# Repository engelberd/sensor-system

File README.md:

# sensor-system

This repository contains the full Sensor System project:

- `hardware/` for KiCad PCB projects, parts, footprints, and hardware notes
- `node/` for the Pico firmware and bootloader artifacts
- `host/` for the complete host product: configuration, operator support and runtime
- `host/runtime/` for the Rust recorder, protocol-6 contracts and data tools

Architecture and current implementation gates start at
[docs/README.md](docs/README.md). The supported local operator interface is
[hostctl v2](docs/architecture/HOSTCTL-V2.md).

For a macOS KiCad, firmware and host-development workstation, follow
[the macOS setup guide](docs/SETUP-MACOS.md), install declared tools with
`brew bundle --file Brewfile`, and run `./tools/check_macos.sh`.

The generated, ignored `host/system_config.json` extends a tracked profile from
`host/configs/systems/`. Product-wide defaults live in
`host/configs/common.json`; stable channel and sensor facts live in the system
profile; device paths, storage overrides and temporary disabled channels remain
in the local overlay. See [the repository structure](docs/REPOSITORY-STRUCTURE.md)
and validate an installation with:

```bash
./hostctl doctor --config host/system_config.json
```

Release validation and publication are described in
[RELEASING.md](RELEASING.md), and notable changes are listed in
[CHANGELOG.md](CHANGELOG.md).

Local runtime output has one predictable layout:

- `var/recordings/` for new measurements
- `var/archive/` for compacted archives
- `var/log/` for host logs and events
- `var/tmp/` for temporary artifacts
- `/run/sensor-system/` for locks, commands and live status

These directories are not versioned. Use `./hostctl paths` to display the
effective paths for the active host configuration.

Every installed node has an immutable hardware revision. Revision `2` is the
currently installed wiring (SCK 14, MOSI 15, DRDY 11, INT1 10, no DE GPIO),
while revision `1` uses SCK 10, MOSI 11, DRDY 14, INT1 15 and DE on GPIO2.
Node IDs and sensor settings remain runtime configuration independent of that
revision.

## Repository Notes

In this Codex workspace the top-level `.git/` path is reserved by the
environment, so repository metadata lives in `.git-main/` and the local wrapper
`./sgit` should be used instead of plain `git`.

Suggested day-to-day workflow in this workspace:

1. Make changes locally in this repository.
2. Use `./sgit ...` for repository commands in this environment.
3. Commit before flashing or deploying to another device.
4. Push to your remote.
5. On the Raspberry Pi host, run `git pull`, build from `node/`, and flash the selected artifact.

## Local Bring-Up On A New Computer

If you are building and flashing from a local Linux or macOS machine instead of
the Raspberry Pi host:

1. Clone the repository and enter it.
2. Install the Pico SDK and toolchain.
3. Build `node/`.
4. Flash `node/build/sensor-system-node-factory.uf2` onto a brand-new Pico 2.
5. Build the host with `./hostctl build`.
6. Identify the node read-only with `./hostctl node identify DEVICE ADDRESS 115200`.

Example setup for a clean local checkout:

```bash
git clone git@github.com:engelberd/sensor-system.git
cd sensor-system
git clone https://github.com/raspberrypi/pico-sdk.git
export PICO_SDK_PATH=$PWD/pico-sdk
python3 -m venv host/.venv
host/.venv/bin/python -m pip install -r host/requirements-recorder.txt
```

The local `pico-sdk/` checkout is intentionally ignored and is not a submodule.
Each build host may keep the SDK elsewhere and point `PICO_SDK_PATH` to it.

On macOS with Homebrew, the typical firmware toolchain is:

```bash
brew install cmake picotool arm-none-eabi-gcc
```

Build the node firmware with explicit compiler paths when needed:

```bash
cmake -S node --preset board-v2 \
  -DCMAKE_C_COMPILER=/opt/homebrew/bin/arm-none-eabi-gcc \
  -DCMAKE_CXX_COMPILER=/opt/homebrew/bin/arm-none-eabi-g++ \
  -DCMAKE_ASM_COMPILER=/opt/homebrew/bin/arm-none-eabi-gcc
cmake --build node/build
```

For a V1 board use `cmake -S node --preset board-v1` followed by
`cmake --build node/build.v1`. Never reuse one build directory for both board
revisions.

The most important output files are:

- `node/build/sensor-system-node-factory.uf2` for first-time USB/BOOTSEL flashing
- `node/build/sensor-system-node.uf2` as the general full-image UF2
- `node/build/sensor-system-node-update-package.json` for later RS485 updates

Further details live in:

- [hardware/README.md](hardware/README.md)
- [node/README-bootloader.md](node/README-bootloader.md)
- [host/README-product.md](host/README-product.md)
- [host/README-deploy.md](host/README-deploy.md)

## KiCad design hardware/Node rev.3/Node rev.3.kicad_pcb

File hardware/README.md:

# Hardware

Hardware design files for the Sensor System project.

Current KiCad project:

- `KiCad - node V2/RP2350.kicad_pro`

The directory name is historical. This is an unreleased custom-board design,
not the definition of the V2 boards installed in Sanok. Installed V2 wiring is
defined by `node/config/board_profile.h`: SCK 14, MOSI 15, MISO 12, CS 13,
DRDY 11, INT1 10 and no firmware-controlled DE pin. Do not change the firmware
revision map from the in-progress KiCad project without a physical bring-up and
an explicit new board revision.

## Repository layout

This project should stay as one GitHub repository for now:

- `hardware/` - KiCad projects, PCB notes, parts, footprints, manufacturing files
- `node/` - RP2350/Pico firmware
- `host/` - host tools, recorder, dashboards, deployment files

This is a monorepo layout. It is simpler than a nested Git repository and makes
hardware/software changes easy to review together. A separate hardware repository
or Git submodule only starts to pay off if the PCB must be shared with a different
team, licensed differently, or released on a different schedule.

## What is tracked

Track these files:

- `*.kicad_pro`
- `*.kicad_sch`
- `*.kicad_pcb`
- project-local `*.kicad_sym` files
- project-local `*.pretty/*.kicad_mod` footprint libraries
- selected 3D models used by footprints
- documentation in this directory
- released fabrication outputs in a named release folder, if needed

Do not track these files:

- `*.kicad_prl`
- `*-backups/`
- `fp-info-cache`
- local lock/temp files
- `.DS_Store`

## Collaboration rules

- Commit before making large schematic rewires or PCB placement changes.
- Pull before opening KiCad if someone else may have pushed hardware changes.
- Avoid editing the same schematic sheet or PCB placement in parallel.
- For footprint changes, edit project-local libraries first, then update the
  board from the library and commit both the library change and board change.
- Put part decisions in `parts.md` before layout, especially when package,
  stock, or footprint choice matters.
- Put JLCPCB/LCSC assembly candidates and stock checks in `jlcpcb-parts.md`.
- Put layout/manufacturing decisions in `design-notes.md`.
- Track current work, assumptions, tasks, and completed items in `progress.md`.

## Opening the project

Open this file in KiCad:

```text
hardware/KiCad - node V2/RP2350.kicad_pro
```

If a footprint is missing, first check the project-local library:

```text
hardware/KiCad - node V2/my_footprints.pretty
```

Vendor downloads and raw imported libraries can stay locally in
`footprints.extra/`, which is ignored by Git. After checking a vendor footprint,
copy the cleaned version into `my_footprints.pretty` so everyone gets the same
reviewed footprint.

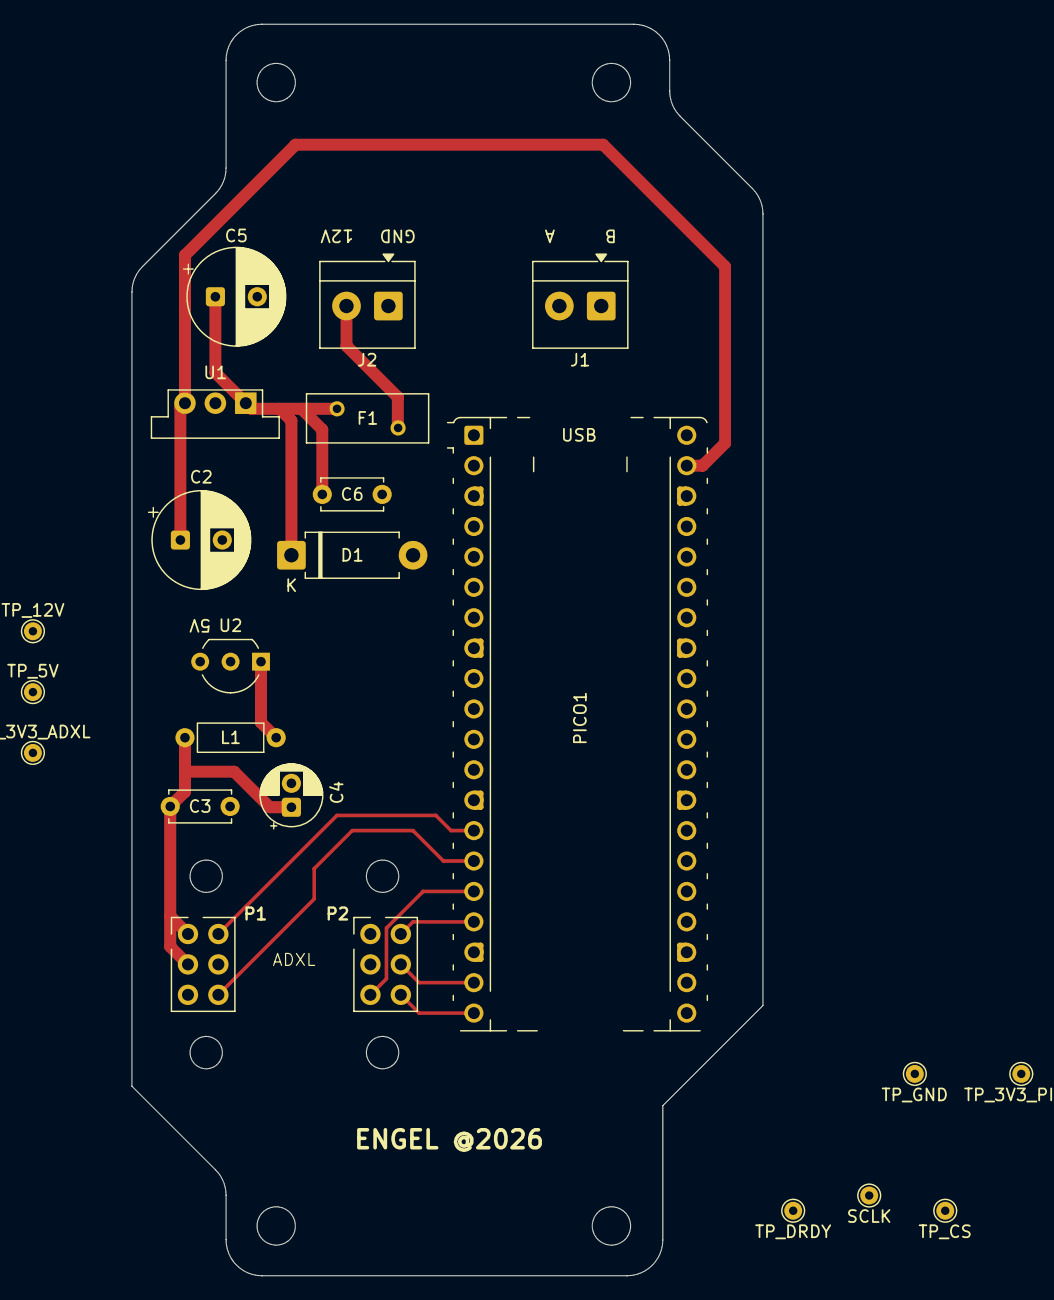
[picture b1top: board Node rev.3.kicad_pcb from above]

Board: 2 copper layers, 52.7 x 104.5 mm, 26 parts (0 on the bottom side), 13 nets.

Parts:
C2: 220uF; CP_Radial_D8.0mm_P3.50mm
C3, C6: 100nF; C_Disc_D5.0mm_W2.5mm_P5.00mm
C4: 10uF; CP_Radial_D5.0mm_P2.00mm
C5: 470uF; CP_Radial_D8.0mm_P3.50mm
D1: P6KE15A-DIO; D_DO-15_P10.16mm_Horizontal
F1: MF-R050; Fuse_BelFuse_0ZRE0016FF_L9.9mm_W3.8mm
H1, H2, H3, H4: MountingHole; MountingHole_3.2mm_M3
J1, J2: Screw_Terminal_01x02; TerminalBlock_4Ucon_1x02_P3.50mm_Horizontal
L1: FRH035080-A; L_Axial_L5.3mm_D2.2mm_P7.62mm_Horizontal_Vishay_IM-1
MOD1: EVAL-ADXL355Z
PICO1: RaspberryPi_Pico; RaspberryPi_Pico_Common_Unspecified
TP1: TP_5V; TestPoint_THTPad_D1.5mm_Drill0.7mm
TP2: TP_GND; TestPoint_THTPad_D1.5mm_Drill0.7mm
TP3: TP_12V; TestPoint_THTPad_D1.5mm_Drill0.7mm
TP6: TP_3V3_ADXL; TestPoint_THTPad_D1.5mm_Drill0.7mm
TP7: TP_3V3_PICO; TestPoint_THTPad_D1.5mm_Drill0.7mm
TP8: SCLK; TestPoint_THTPad_D1.5mm_Drill0.7mm
TP9: TP_CS; TestPoint_THTPad_D1.5mm_Drill0.7mm
TP10: TP_DRDY; TestPoint_THTPad_D1.5mm_Drill0.7mm
U1: OKI-78SR-5_1_5-W36-C; Converter_DCDC_Murata_OKI-78SR_Vertical
U2: LP2950CZ-3.3/NOPB; TO-92_Inline_Wide

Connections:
/3V3_ADXL: C3.1, C4.1, L1.2, MOD1.1 (VDDIO), MOD1.3 (VDD), TP6.1 (1_1)
/3V3_Pico: PICO1.36 (3V3), TP7.1 (1_1)
/5V: C2.1, PICO1.39 (VSYS), TP1.1 (1_1), U1.3 (Positive_Output), U2.3 (IN)
/12VIN: F1.2, J2.2
/ADXL CS: MOD1.8 (CS/SCL), PICO1.17 (GPIO13), TP9.1 (1_1)
/ADXL DRDY: MOD1.6 (DRDY), PICO1.15 (GPIO11), TP10.1 (1_1)
/ADXL INT1: MOD1.2 (INT1), PICO1.14 (GPIO10)
/ADXL SCLK: MOD1.10 (SCLK/VSSIO), PICO1.19 (GPIO14), TP8.1 (1_1)
/ADXL SDI: MOD1.12 (MOSI/SDA), PICO1.20 (GPIO15)
/ADXL SDO: MOD1.11 (MISO/SDA), PICO1.16 (GPIO12)
GND: C2.2, C3.2, C4.2, C5.2, C6.2, D1.2 (A), J2.1, MOD1.5 (GND), PICO1.3 (GND), PICO1.8 (GND), PICO1.13 (GND), PICO1.18 (GND), PICO1.23 (GND), PICO1.28 (GND), PICO1.38 (GND), TP2.1 (1_1), U1.2 (Common_(Ground)), U2.2 (GND)
unnamed: C5.1, C6.1, D1.1 (K), F1.1, TP3.1 (1_1), U1.1 (Positive_Input)
unnamed: L1.1, U2.1 (OUT)

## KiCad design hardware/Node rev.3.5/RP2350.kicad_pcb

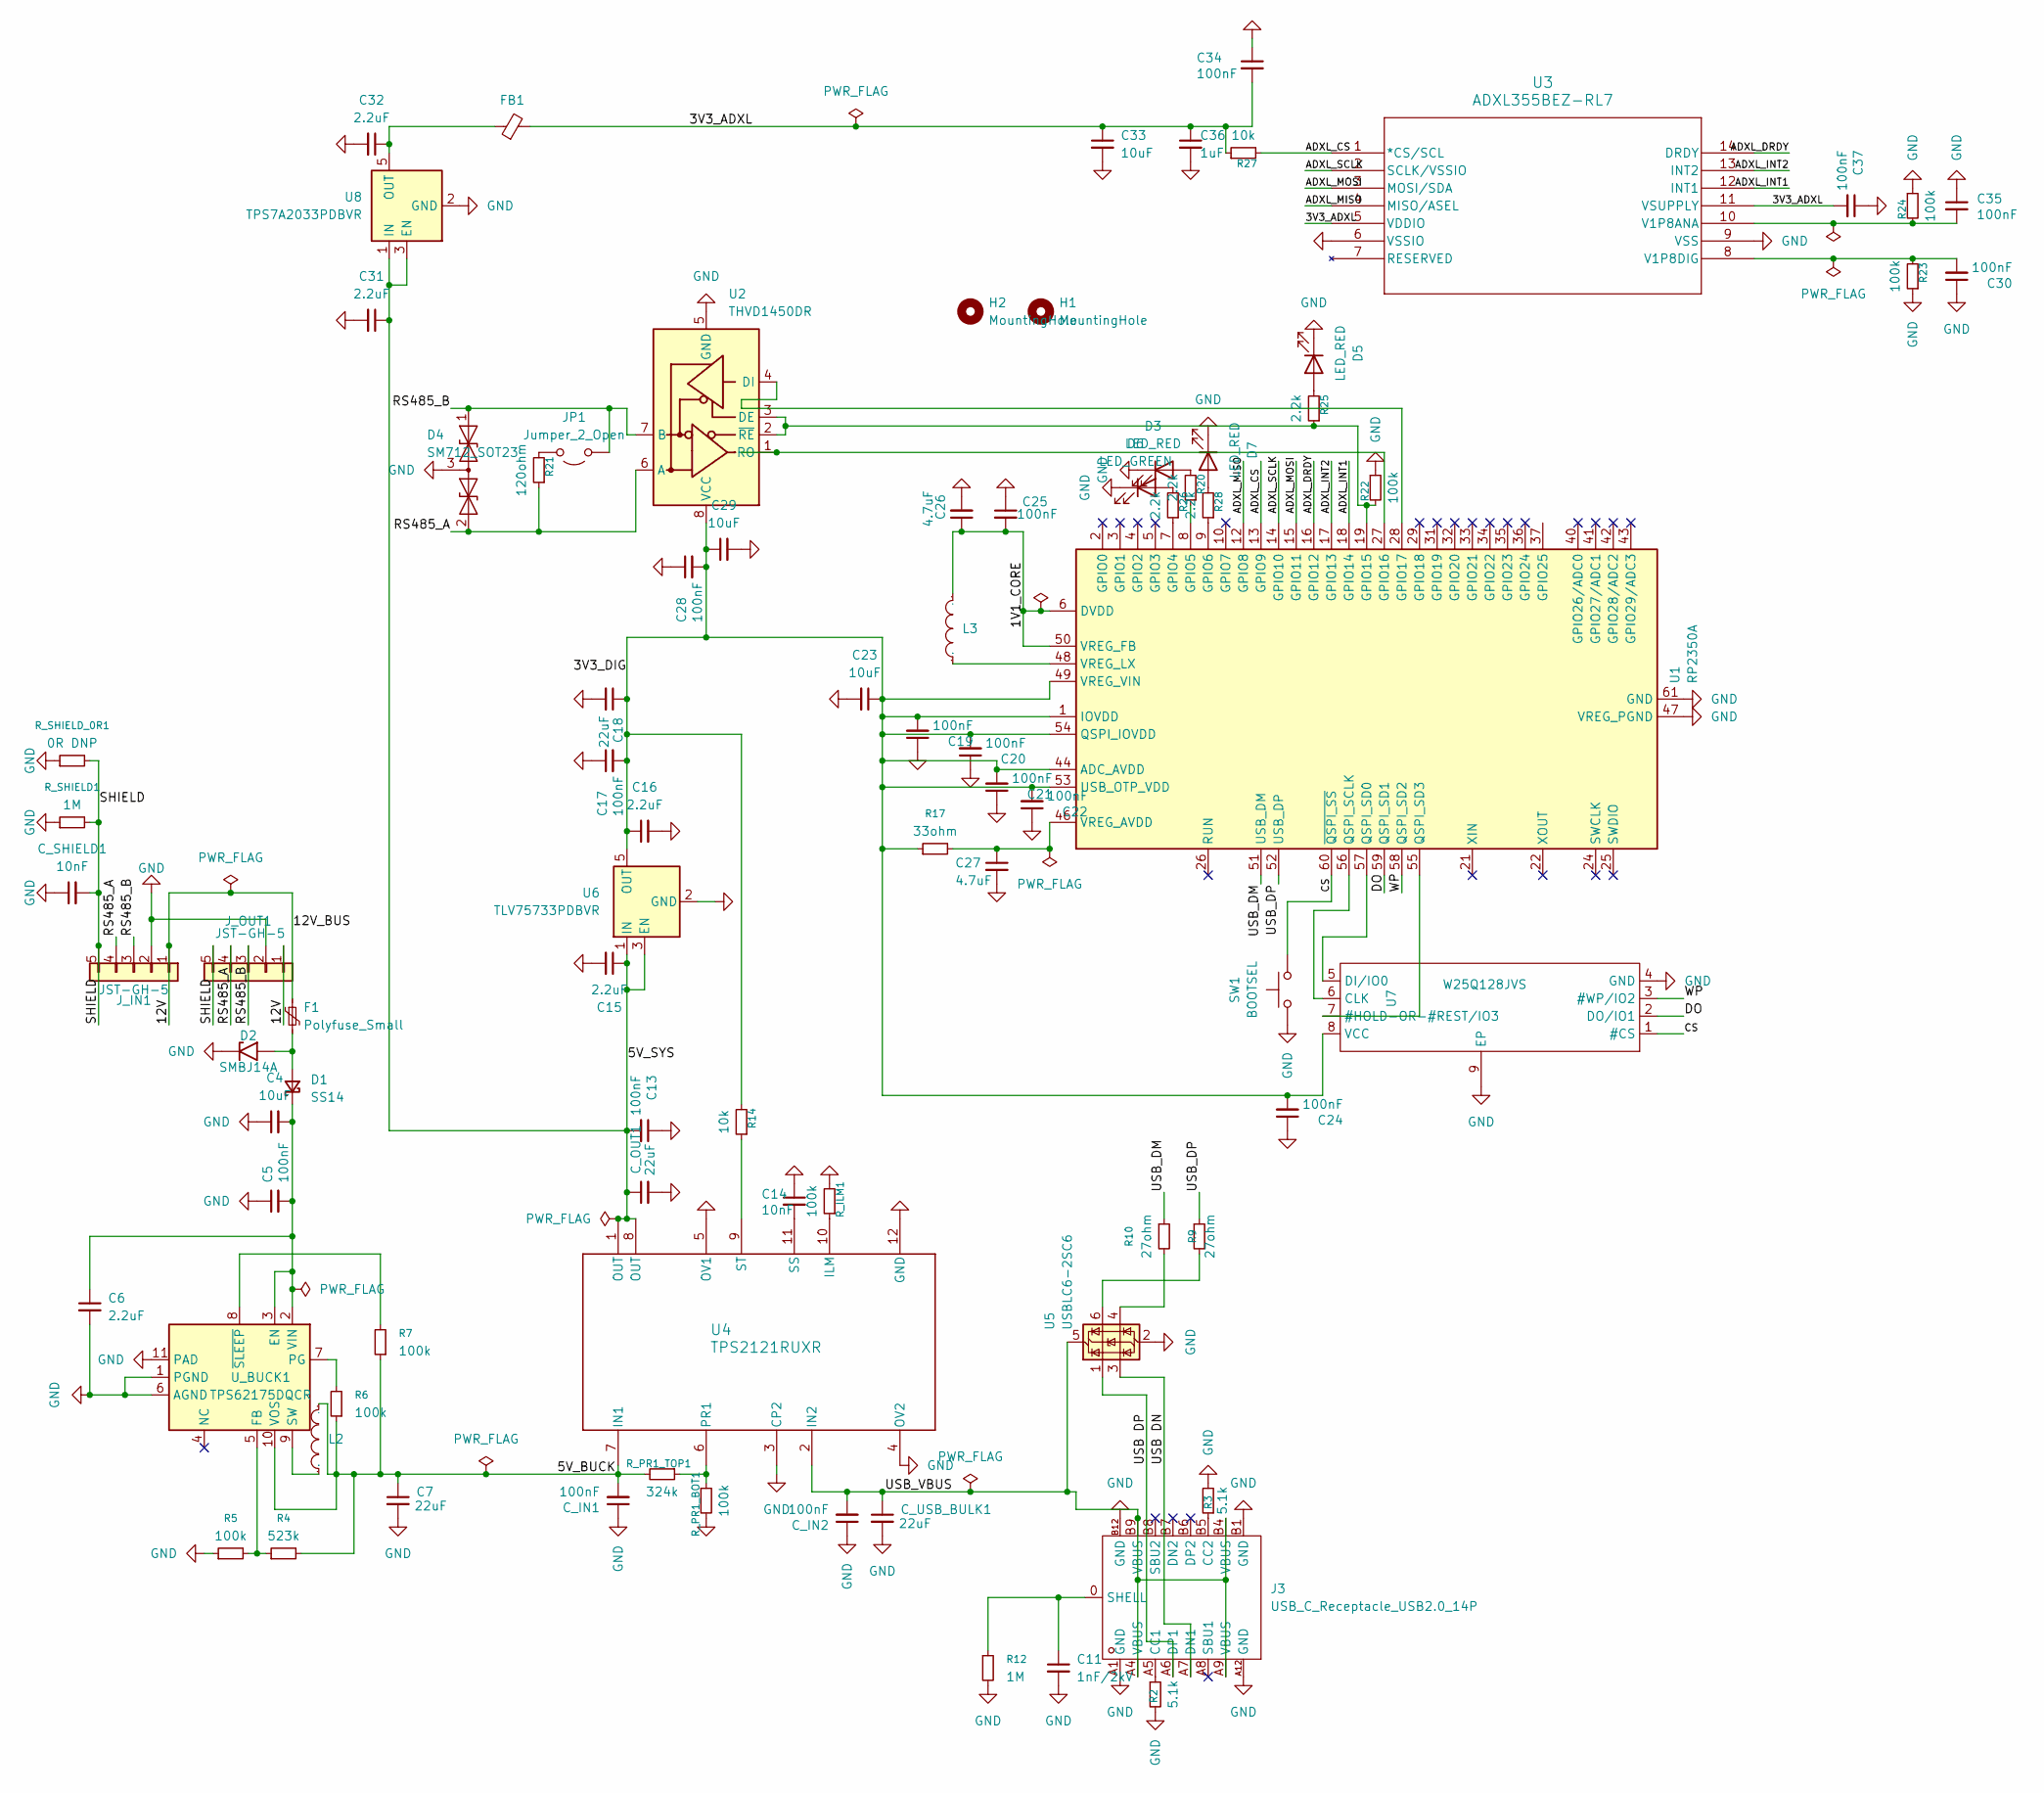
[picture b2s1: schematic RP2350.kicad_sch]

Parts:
C4, C29, C33: 10uF; C_0805_2012Metric
C5, C17, C28: 100nF; C_0603_1608Metric
C6, C15, C16, C31, C32: 2.2uF; C_0805_2012Metric
C7, C18: 22uF; C_0805_2012Metric
C11: 1nF/2kV; C_1206_3216Metric
C13, C19, C20, C21, C22, C24, C25, C30, C34, C35, C37: 100nF; C_0402_1005Metric
C14: 10nF; C_0603_1608Metric
C23: 10uF; C_0603_1608Metric
C26: 4.7uF; C_0603_1608Metric
C27: 4.7uF; C_0805_2012Metric
C36: 1uF; C_0603_1608Metric
C_IN1, C_IN2: 100nF; C_0402_1005Metric
C_OUT1: 22uF; C_0805_2012Metric
C_SHIELD1: 10nF; C_0805_2012Metric
C_USB_BULK1: 22uF; C_0805_2012Metric
D1: SS14; D_SMA; Manufacturer Part SS14; JLCPC# SS14
D2: SMBJ14A; D_SMB; Manufacturer Part SMBJ14A; JLCPC# C29937
D3, D5, D7: LED_RED; LED_0603_1608Metric; Manufacturer Part KT-0603R; JLCPC# 0603
D4: SM712_SOT23; SOT-23; Manufacturer Part SM712.TCT; JLCPC# C12067
D6: LED_GREEN; LED_0805_2012Metric; Manufacturer Part KT-0805G; JLCPC# C2297
F1: Polyfuse_Small; Fuse_1812_4532Metric; Manufacturer Part 1812L150/24MR; JLCPC# C142805
FB1: FerriteBead_S; L_0805_2012Metric; Manufacturer Part MPZ2012S601AT000; JLCPC# C21519
H1, H2: MountingHole; MountingHole_2.5mm
J3: USB_C_Receptacle_USB2.0_14P; USB-C-SMD_GT-USB-7051A; Manufacturer Part GT-USB-7051A; LCSC Part Name Type-C 母 立贴
JP1: Jumper_2_Open; SolderJumper-2_P1.3mm_Open_Pad1.0x1.5mm
J_IN1: JST-GH-5; CONN-SMD_BM05B-GHS-TBT; Manufacturer Part BM05B-GHS-TBT(LF)(SN)(N); JLCPC# C189891
J_OUT1: JST-GH-5; CONN-SMD_BM05B-GHS-TBT; Manufacturer Part BM05B-GHS-TBT(LF)(SN)(N); JLCPC# C189891
L2: 10uH; FXL0420-100-MIND-SMD_L4.4-W4.2; Manufacturer Part FXL0420-100-M; LCSC Part Name 10uH ±20% 2.2A
L3: 3.3uH; IND-SMD_L2.0-W1.6_AOTA-B201610S3R3-101-T; Manufacturer Part AOTA-B201610S3R3-101-T; LCSC Part Name 3.3uH 2.4A
R2, R3: 5.1k; R_0402_1005Metric
R4: 523k; R_0402_1005Metric
R5, R6, R7, R23, R24: 100k; R_0402_1005Metric
R9, R10: 27ohm; R_0402_1005Metric
R12: 1M; R_0603_1608Metric
R14, R27: 10k; R_0402_1005Metric
R17: 33ohm; R_0402_1005Metric
R20, R25, R26, R28: 2.2k; R_0402_1005Metric
R21: 120ohm; R_0805_2012Metric
R22: 100k; R_0603_1608Metric
R_ILM1: 100k; R_0402_1005Metric
R_PR1_BOT1: 100k; R_0402_1005Metric
R_PR1_TOP1: 324k; R_0402_1005Metric
R_SHIELD1: 1M; R_0603_1608Metric
R_SHIELD_0R1: 0R DNP; R_0805_2012Metric
SW1: BOOTSEL; KEY-SMD_4P-L4.2-W3.2-P2.20-LS4.6; Manufacturer Part SKRPACE010; JLCPC# C139797
U1: RP2350A; QFN-60-1EP_7x7mm_P0.4mm_EP3.4x3.4mm; JLCPC# C42411118
U2: THVD1450DR; THVD1450DR-SOIC-8_L4.9-W3.9-P1.27-LS6.0-BL; JLCPC# C2671361
U3: ADXL355BEZ-RL7; JLCPC# C515892
U4: TPS2121RUXR; TPS2121RUXR-VQFN-HR-12_L2.5-W2.0-P0.50-BL; JLCPC# C485916
U5: USBLC6-2SC6; JLCPC# C7519
U6: TLV75733PDBVR; TLV75733PDBVR-SOT-23-5_L2.9-W1.6-P0.95-LS2.8-BL; Manufacturer Part TLV75733PDBVR; JLCPC# C485517
U7: W25Q128JVS; WSON-8_L6.0-W5.0-P1.27-BL-EP; Manufacturer Part W25Q128JVPIQ; LCSC Part Name 支持双路/四路SPI接口的3V、128Mbit 串行闪存
U8: TPS7A2033PDBVR; Manufacturer Part TPS7A2033PDBVR; JLCPC# C2862740
U_BUCK1: TPS62175DQCR; TPS62175DQCR_WSON-10_L3.0-W2.0-P0.50-BL-EP; Manufacturer Part TPS62175DQCR; LCSC C32097

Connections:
/1V1_CORE: C25.2, C26.1, L3.2, U1.6 (DVDD), U1.23 (DVDD), U1.39 (DVDD), U1.50 (VREG_FB)
/3V3_ADXL: C33.1, C34.2, C36.1, C37.2, FB1.2, R27.1, U3.5 (VDDIO), U3.11 (VSUPPLY)
/3V3_DIG: C16.1, C17.2, C18.1, C19.2, C20.2, C21.2, C22.2, C23.1, C24.2, C28.2, C29.1, R14.2, R17.1, U1.1 (IOVDD), U1.11 (IOVDD), U1.20 (IOVDD), U1.30 (IOVDD), U1.38 (IOVDD), U1.44 (ADC_AVDD), U1.45 (IOVDD), U1.49 (VREG_VIN), U1.53 (USB_OTP_VDD), U1.54 (QSPI_IOVDD), U2.8 (VCC), U6.5 (OUT), U7.8 (VCC)
/5V_BUCK: C7.1, C_IN1.2, L2.2, R4.2, R6.1, R7.1, R_PR1_TOP1.2, U4.7 (IN1), U_BUCK1.10 (VOS)
/5V_SYS: C13.2, C15.1, C31.1, C_OUT1.1, U4.1 (OUT), U4.8 (OUT), U6.1 (IN), U6.3 (EN), U8.1 (IN), U8.3 (EN)
/12V: F1.1, J_IN1.1 (12V), J_OUT1.1 (12V)
/ADXL_CS: R27.2, U1.13 (GPIO9), U3.1 (*CS/SCL)
/ADXL_DRDY: U1.16 (GPIO12), U3.14 (DRDY)
/ADXL_INT1: U1.18 (GPIO14), U3.12 (INT1)
/ADXL_INT2: U1.17 (GPIO13), U3.13 (INT2)
/ADXL_MISO: U1.12 (GPIO8), U3.4 (MISO/ASEL)
/ADXL_MOSI: U1.15 (GPIO11), U3.3 (MOSI/SDA)
/ADXL_SCLK: U1.14 (GPIO10), U3.2 (SCLK/VSSIO)
/CS: SW1.2, U1.60 (~QSPI_SS), U7.1 (#CS)
/DO: U1.59 (QSPI_SD1), U7.2 (DO/IO1)
/RS485_A: D4.2 (A2), J_IN1.4 (A), J_OUT1.4 (A), R21.1, U2.6 (A)
/RS485_B: D4.1 (A1), JP1.1 (A), J_IN1.3 (B), J_OUT1.3 (B), U2.7 (B)
/SHIELD: C_SHIELD1.2, J_IN1.5 (SHIELD), J_OUT1.5 (SHIELD), R_SHIELD1.2, R_SHIELD_0R1.2
/USB DN: J3.A7 (DN1), U5.3 (I/O2)
/USB DP: J3.A6 (DP1), U5.1 (I/O1)
/USB_DM: R10.1, U1.51 (USB_DM)
/USB_DP: R9.1, U1.52 (USB_DP)
/USB_VBUS: C_IN2.2, C_USB_BULK1.1, J3.A4 (VBUS), J3.A9 (VBUS), J3.B4 (VBUS), J3.B9 (VBUS), U4.2 (IN2), U5.5 (VBUS)
/WP: U1.58 (QSPI_SD2), U7.3 (#WP/IO2)
GND: C4.1, C5.1, C6.2, C7.2, C11.2, C13.1, C14.1, C15.2, C16.2, C17.1, C18.2, C19.1, C20.1, C21.1, C22.1, C23.2, C24.1, C25.1, C26.2, C27.2, C28.1, C29.2, C30.1, C31.2, C32.2, C33.2, C34.1, C35.1, C36.2, C37.1, C_IN1.1, C_IN2.1, C_OUT1.2, C_SHIELD1.1, C_USB_BULK1.2, D2.1 (A1), D3.1 (K), D4.3 (common), D5.1 (K), D6.1 (K), D7.1 (K), J3.A1 (GND), J3.A12 (GND), J3.B1 (GND), J3.B12 (GND), J_IN1.2 (GND), J_OUT1.2 (GND), R2.2, R3.2, R5.1, R12.2, R22.1, R23.1, R24.1, R_ILM1.2, R_PR1_BOT1.2, R_SHIELD1.1, R_SHIELD_0R1.1, SW1.1, U1.47 (VREG_PGND), U1.61 (GND), U2.5 (GND), U3.6 (VSSIO), U3.9 (VSS), U4.3 (CP2), U4.4 (OV2), U4.5 (OV1), U4.12 (GND), U5.2 (GND), U6.2 (GND), U7.4 (GND), U7.9 (EP), U8.2 (GND), U_BUCK1.1 (PGND), U_BUCK1.6 (AGND), U_BUCK1.11 (PAD)
unnamed: D1.2 (A), D2.2 (A2), F1.2
unnamed: C4.2, C5.2, C6.1, D1.1 (K), U_BUCK1.2 (VIN), U_BUCK1.3 (EN)
unnamed: D3.2 (A), R20.2
unnamed: D5.2 (A), R25.2
unnamed: D6.2 (A), R26.2
unnamed: D7.2 (A), R28.2
unnamed: J3.A5 (CC1), R2.1
unnamed: J3.B5 (CC2), R3.1
unnamed: C11.1, J3.0 (SHELL), R12.1
unnamed: JP1.2 (B), R21.2
unnamed: R9.2, U5.6 (I/O1)
unnamed: R10.2, U5.4 (I/O2)
unnamed: R26.1, U1.7 (GPIO4)
unnamed: R20.1, U1.8 (GPIO5)
unnamed: R28.1, U1.9 (GPIO6)
unnamed: R22.2, R25.1, U1.19 (GPIO15), U2.2 (~RE), U2.3 (DE)
unnamed: U1.27 (GPIO16), U2.1 (RO)
unnamed: U1.28 (GPIO17), U2.4 (DI)
unnamed: U1.56 (QSPI_SCLK), U7.6 (CLK)
unnamed: U1.57 (QSPI_SD0), U7.5 (DI/IO0)
unnamed: U1.55 (QSPI_SD3), U7.7 (#HOLD-OR-#REST/IO3)
unnamed: C27.1, R17.2, U1.46 (VREG_AVDD)
unnamed: L3.1, U1.48 (VREG_LX)
unnamed: C35.2, R24.2, U3.10 (V1P8ANA)
unnamed: C30.2, R23.2, U3.8 (V1P8DIG)
unnamed: R_ILM1.1, U4.10 (ILM)
unnamed: R_PR1_BOT1.1, R_PR1_TOP1.1, U4.6 (PR1)
unnamed: C14.2, U4.11 (SS)
unnamed: R14.1, U4.9 (ST)
unnamed: C32.1, FB1.1, U8.5 (OUT)
unnamed: R4.1, R5.2, U_BUCK1.5 (FB)
unnamed: R6.2, U_BUCK1.7 (PG)
unnamed: L2.1, U_BUCK1.9 (SW)
unnamed: R7.2, U_BUCK1.8 (~SLEEP)

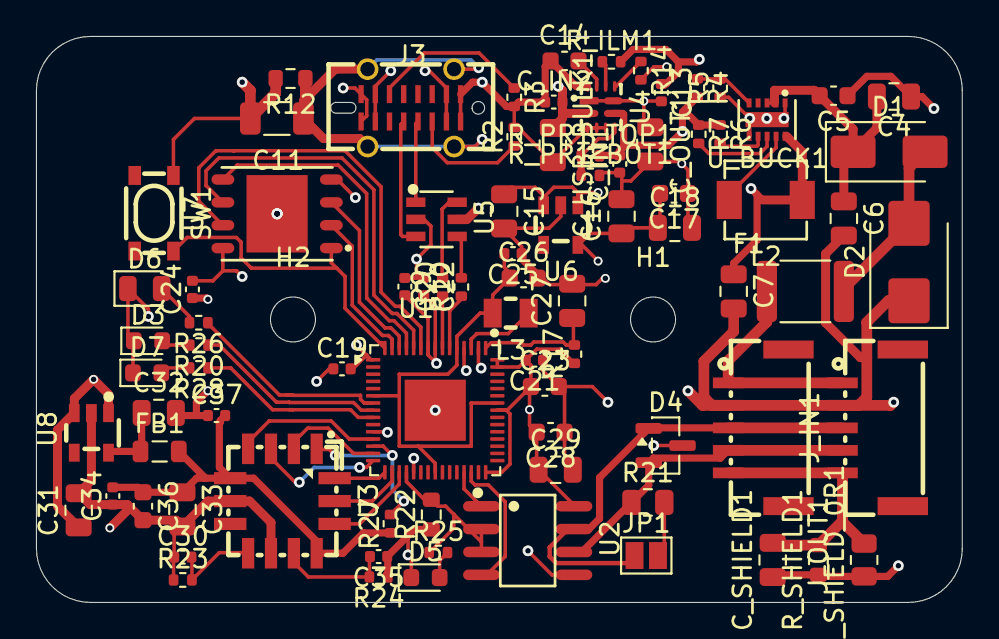
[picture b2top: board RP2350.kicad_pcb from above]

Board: 4 copper layers, 51.4 x 31.4 mm, 87 parts (0 on the bottom side), 59 nets.

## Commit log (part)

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2026-05-21 Rename project to sensor-system
2026-05-21 Update docs and rename workflow
2026-05-22 Update ADXL355 pin mapping
2026-05-22 Update host config for current hardware
2026-05-23 Add node release packaging
2026-05-30 hardware: add KiCad project and collaboration notes
2026-05-30 docs: update bootloader README assets
2026-05-30 KiCad: J1 terminal update
2026-05-30 hardware: added net classes
2026-05-30 hardware: 2 terminals fix
2026-05-30 hardware: layout progress + many footprints
2026-05-30 hardware: holly f
2026-05-31 hardware: train update
2026-05-31 hardware: 3v3_dig, 1vcore
2026-05-31 hardware: new layout
2026-06-01 hardware: ERC fixes, PWR_FLAG, and net labels
2026-06-01 hardware: layout updates
2026-06-01 hardware: ERC fixes, PWR_FLAG, and net labels pt.2
2026-06-01 hardware: restored good schema with labels and pwr_flags
2026-06-01 work in progress
2026-06-01 hardware: pico pin change, moved mounting holes
2026-06-01 hardware: added footprints, part numbers, layout update
2026-06-16 Improve soak recording workflow
